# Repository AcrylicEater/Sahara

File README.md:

# Sahara - diy 3d printer filament dryer

This is the hardware and software I designed to convert a cheap food dehydrator into a more intelligent and precisely controlled device, with the aim of drying 3d printer filament.

The original product used was a Esperanza Food Dehydrator EKD003.

You set a target temperature, how long you want to dry and then it does the rest.

It is controlled by a STM32, that via relays turn on and off the fan unit and heating unit.

Be aware that this runs on **mains voltage**, so take the necessary precautions. I've implemented as much safety as I deem reasonable, but use at your own risk. I the main board with a external prefabricated 230VAC to 5VDC board and I connect an external RC snubber unit in parallel with the fan.

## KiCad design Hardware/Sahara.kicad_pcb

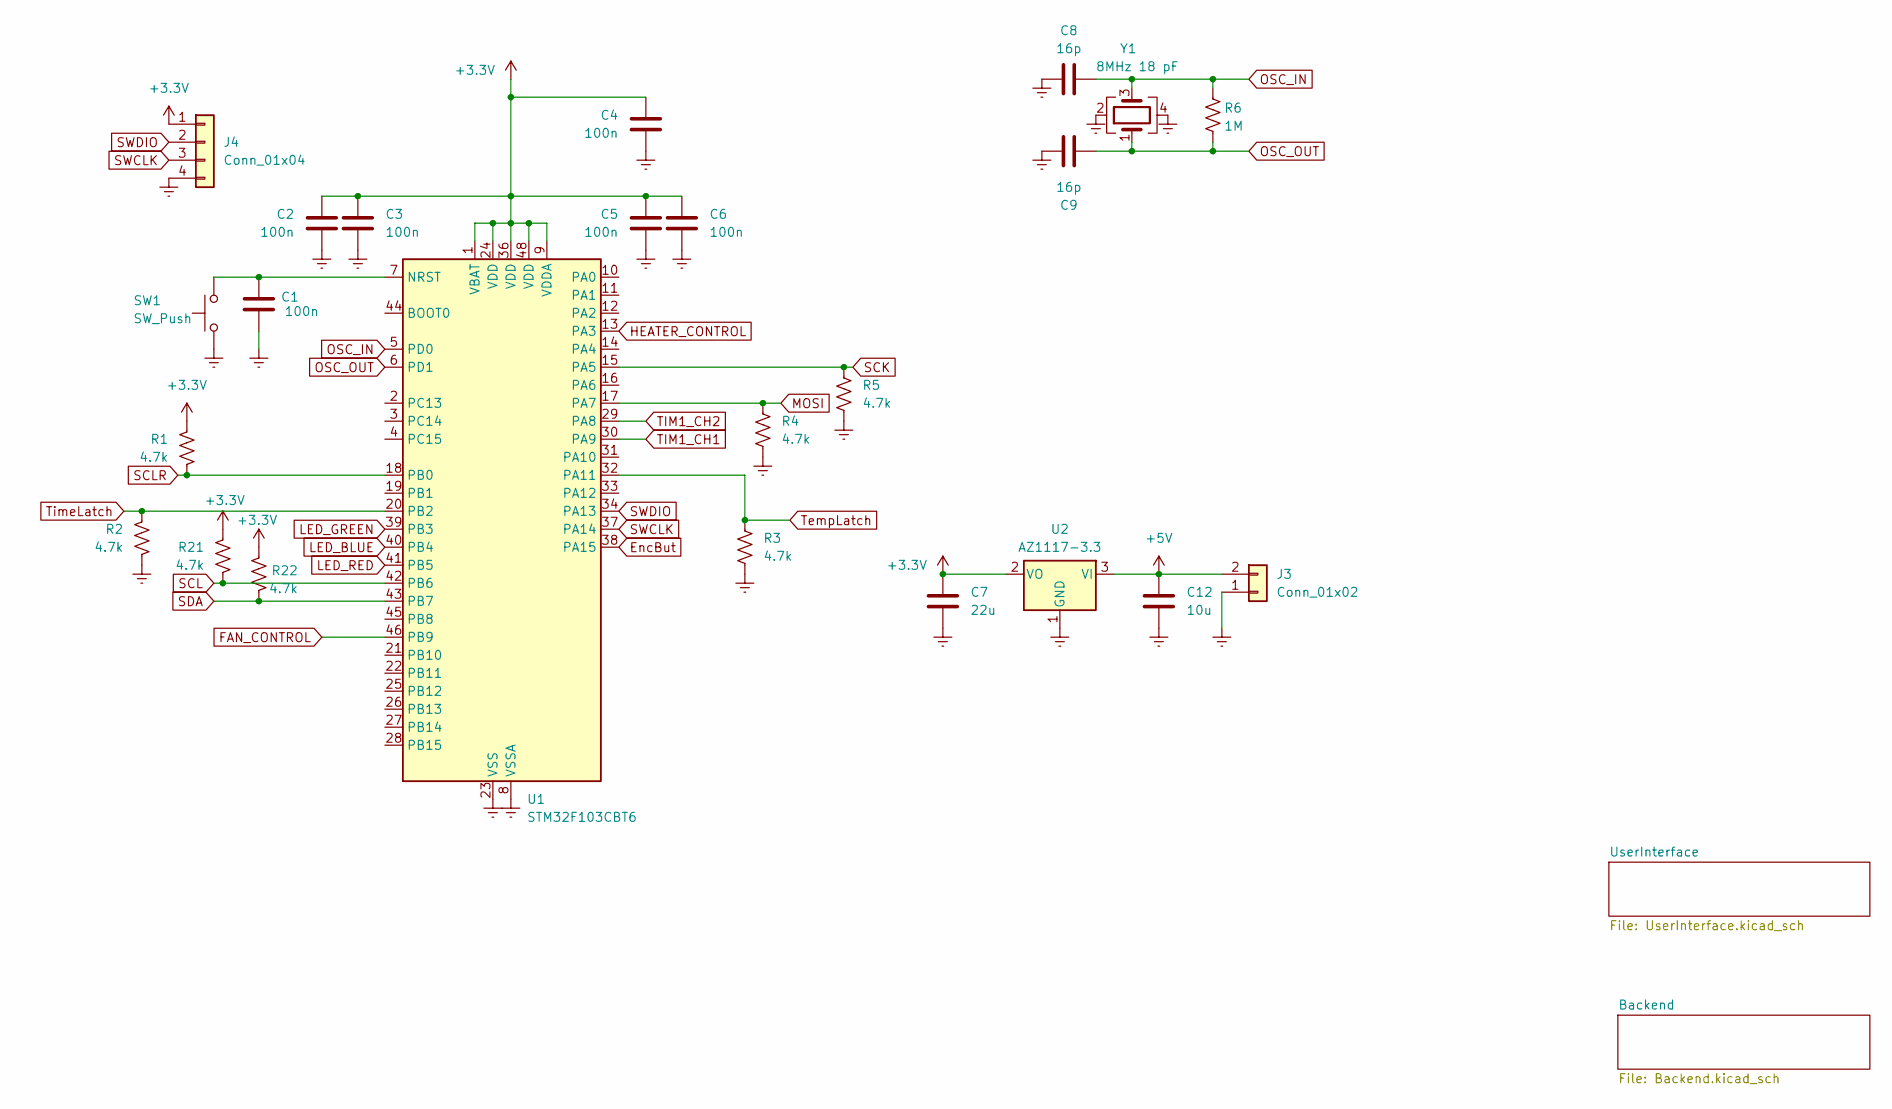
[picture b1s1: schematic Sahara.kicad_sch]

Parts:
C1, C2, C3, C4, C5, C6: 100n; C_0805_2012Metric
C7: 22u; C_0805_2012Metric
C8, C9: 16p; C_0805_2012Metric
C12: 10u; C_0805_2012Metric
J3: Conn_01x02; JST_XH_B2B-XH-AM_1x02_P2.50mm_Vertical
J4: Conn_01x04; JST_XH_B4B-XH-AM_1x04_P2.50mm_Vertical
R1, R2, R3, R4, R5, R21, R22: 4.7k; R_0805_2012Metric
R6: 1M; R_0805_2012Metric
SW1: SW_Push
U1: STM32F103CBT6; LQFP-48_7x7mm_P0.5mm
U2: AZ1117-3.3; SOT230P700X180-4N
Y1: 8MHz 18 pF; Crystal_SMD_TXC_7M-4Pin_3.2x2.5mm

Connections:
+3.3V: C2.1, C3.1, C4.1, C5.1, C6.1, C7.1, J4.1, R1.1, R21.1, R22.1, U1.1 (VBAT), U1.9 (VDDA), U1.24 (VDD), U1.36 (VDD), U1.48 (VDD), U2.2 (VO); also elsewhere on the board
+5V: C12.1, J3.2 (Pin_1), U2.3 (VI); also elsewhere on the board
Earth: C1.2, C2.2, C3.2, C4.2, C5.2, C6.2, C7.2, C8.1, C9.1, C12.2, J3.1 (Pin_2), J4.4, R2.2, R3.2, R4.2, R5.2, SW1.1, U1.8 (VSSA), U1.23 (VSS), U1.35 (VSS), U1.47 (VSS), U2.1 (GND), Y1.2, Y1.4; also elsewhere on the board
EncBut: U1.38 (PA15); also elsewhere on the board
FAN_CONTROL: U1.46 (PB9); also elsewhere on the board
HEATER_CONTROL: U1.13 (PA3); also elsewhere on the board
LED_BLUE: U1.40 (PB4); also elsewhere on the board
LED_GREEN: U1.39 (PB3); also elsewhere on the board
LED_RED: U1.41 (PB5); also elsewhere on the board
MOSI: R4.1, U1.17 (PA7); also elsewhere on the board
unnamed: C1.1, SW1.2, U1.7 (NRST)
OSC_IN: C8.2, R6.1, U1.5 (PD0), Y1.3
OSC_OUT: C9.2, R6.2, U1.6 (PD1), Y1.1
SCK: R5.1, U1.15 (PA5); also elsewhere on the board
SCL: R21.2, U1.42 (PB6); also elsewhere on the board
SCLR: R1.2, U1.18 (PB0); also elsewhere on the board
SDA: R22.2, U1.43 (PB7); also elsewhere on the board
SWCLK: J4.3, U1.37 (PA14)
SWDIO: J4.2, U1.34 (PA13)
TIM1_CH1: U1.30 (PA9); also elsewhere on the board
TIM1_CH2: U1.29 (PA8); also elsewhere on the board
TempLatch: R3.1, U1.32 (PA11); also elsewhere on the board
TimeLatch: R2.1, U1.20 (PB2); also elsewhere on the board

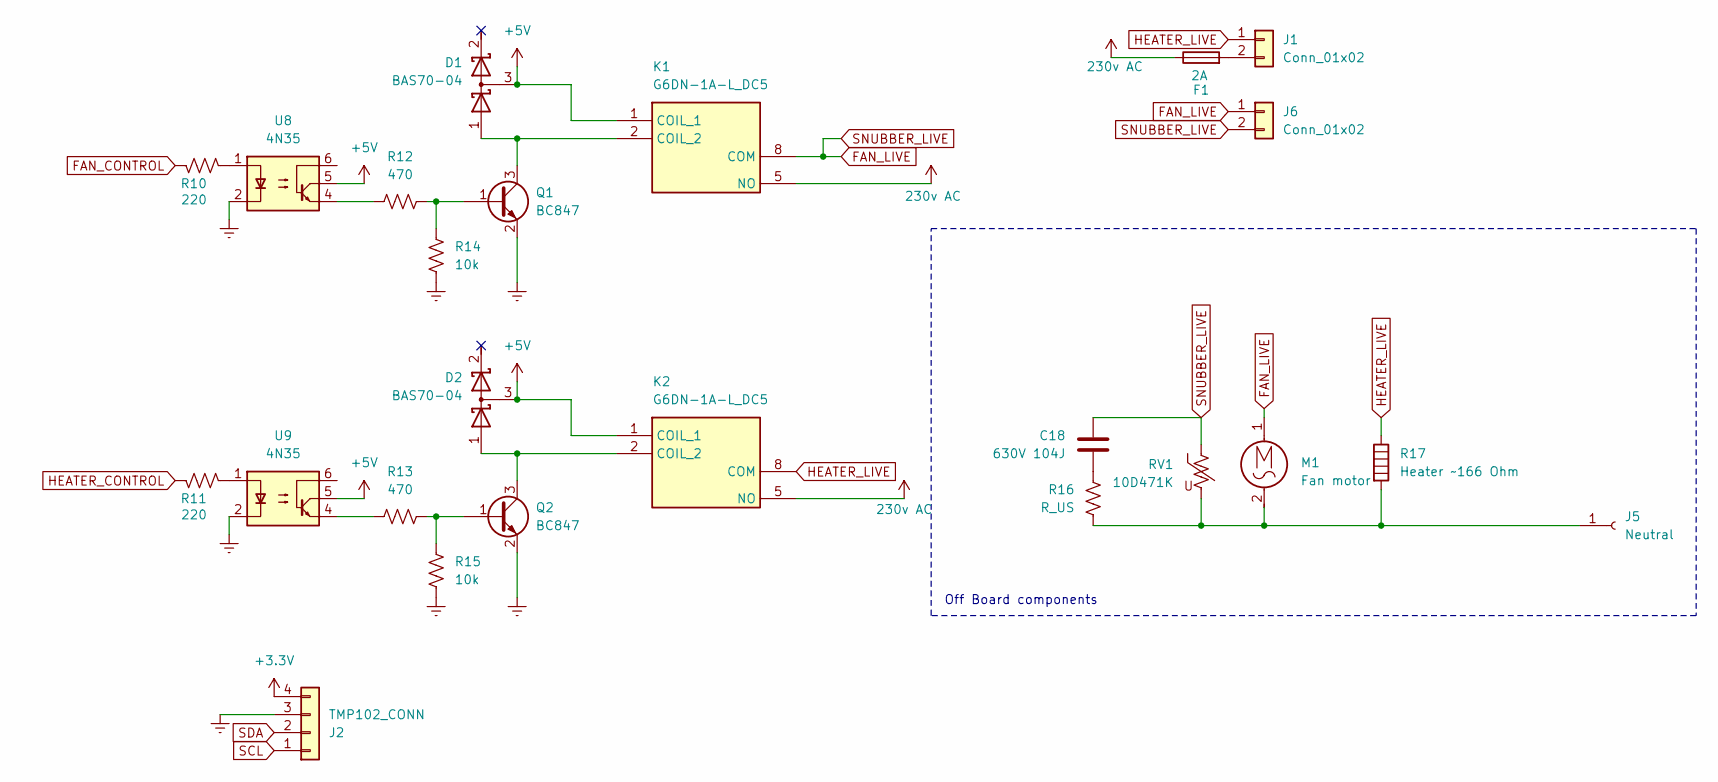
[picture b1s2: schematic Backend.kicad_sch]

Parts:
C18: 630V 104J
D1, D2: BAS70-04; SOT97P230X109-3N; Manufacturer_Part_Number BAS70-04; Mouser Part Number 821-BAS70-04
F1: 2A; WR-FSH_THT_2
J1, J6: Conn_01x02; TerminalBlock_Phoenix_PT-1,5-2-5.0-H_1x02_P5.00mm_Horizontal
J2: TMP102_CONN; JST_XH_B4B-XH-AM_1x04_P2.50mm_Vertical
J5: Neutral
K1, K2: G6DN-1A-L_DC5; G6DN-1A-L; Mouser Part Number 653-G6DN-1A-LDC5
M1: Fan motor
Q1, Q2: BC847; SOT-23
R10, R11: 220; R_0805_2012Metric
R12, R13: 470; R_0805_2012Metric
R14, R15: 10k; R_0805_2012Metric
R16: R_US
R17: Heater ~166 Ohm
RV1: 10D471K
U8, U9: 4N35; 4N35S

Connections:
230v AC: F1.1, K1.5 (NO), K2.5 (NO)
+3.3V: J2.4; also elsewhere on the board
+5V: D1.3 (common), D2.3 (common), K1.1 (COIL_1), K2.1 (COIL_1), U8.5, U9.5; also elsewhere on the board
Earth: J2.3, Q1.2 (E), Q2.2 (E), R14.1, R15.1, U8.2, U9.2; also elsewhere on the board
FAN_CONTROL: R10.2; also elsewhere on the board
FAN_LIVE: C18.1, J6.1, J6.2, K1.8 (COM), M1.1, RV1.1
HEATER_CONTROL: R11.2; also elsewhere on the board
HEATER_LIVE: J1.1, K2.8 (COM), R17.1
unnamed: C18.2, R16.1
unnamed: D1.1 (A), K1.2 (COIL_2), Q1.3 (C)
unnamed: D2.1 (A), K2.2 (COIL_2), Q2.3 (C)
unnamed: F1.2, J1.2
unnamed: J5.1, M1.2, R16.2, R17.2, RV1.2
unnamed: Q1.1 (B), R12.2, R14.2
unnamed: Q2.1 (B), R13.2, R15.2
unnamed: R10.1, U8.1
unnamed: R11.1, U9.1
unnamed: R12.1, U8.4
unnamed: R13.1, U9.4
SCL: J2.1; also elsewhere on the board
SDA: J2.2; also elsewhere on the board

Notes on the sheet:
Off Board components

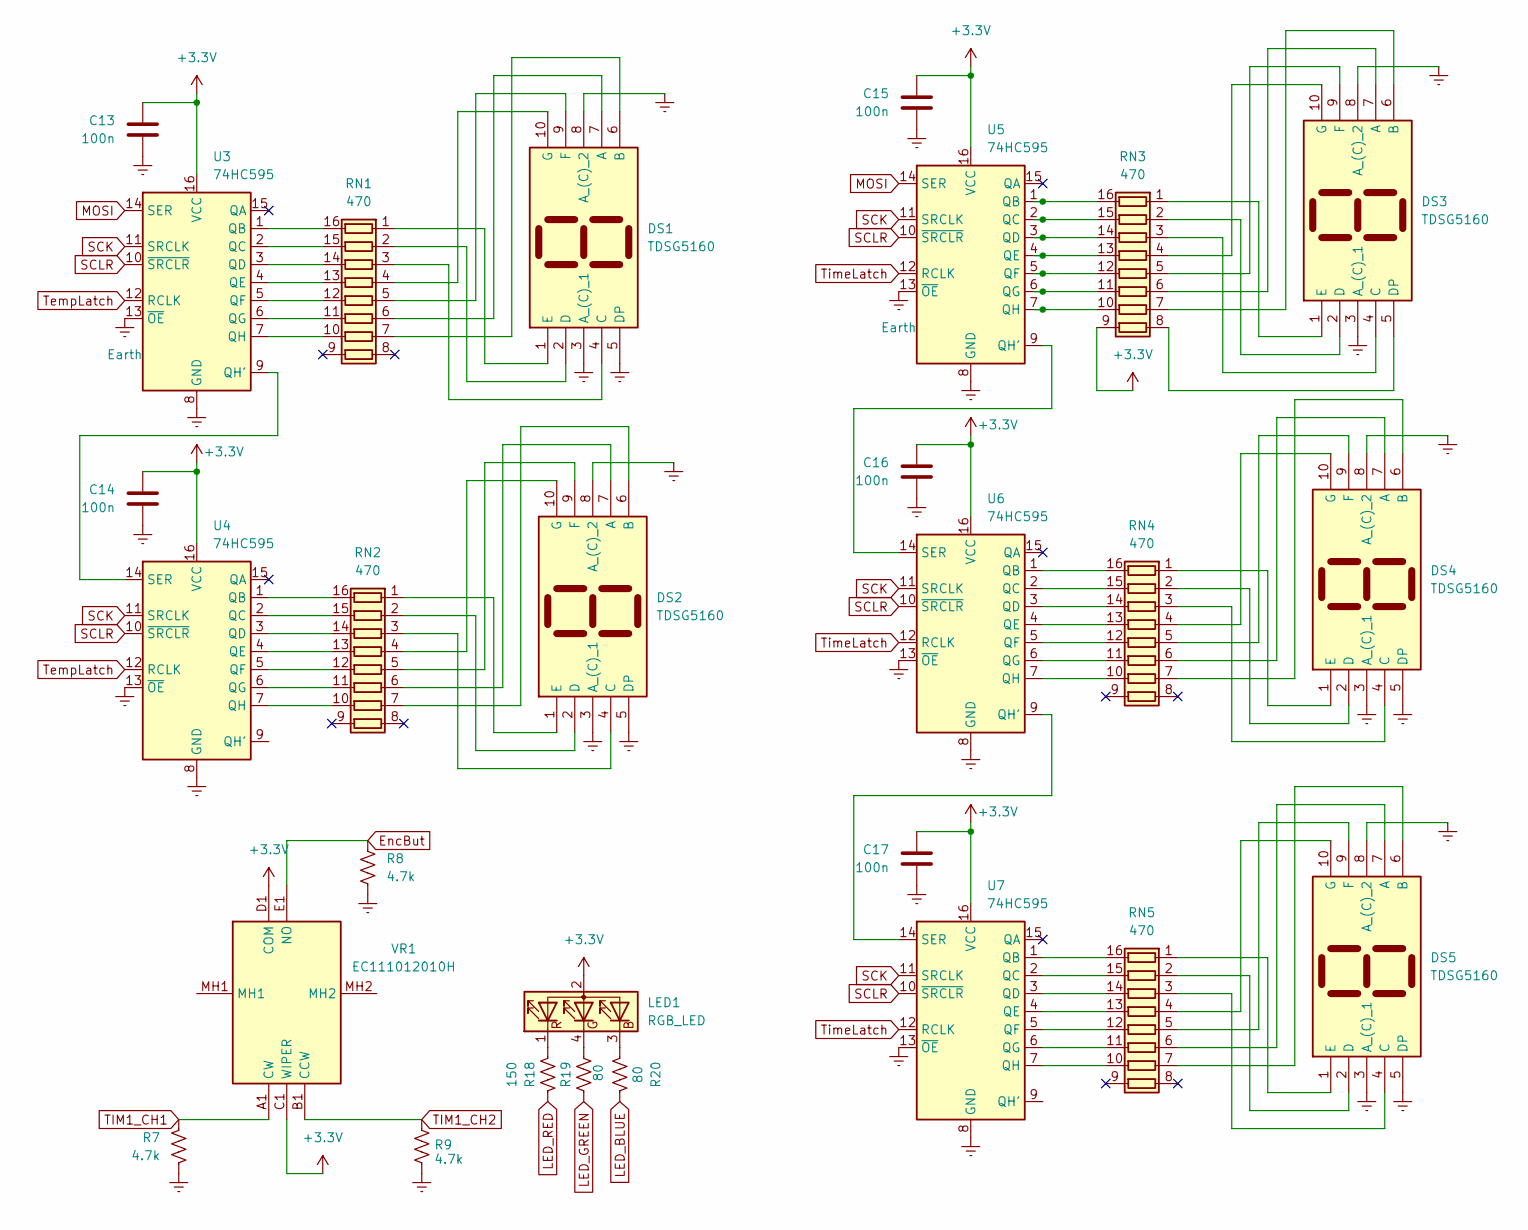
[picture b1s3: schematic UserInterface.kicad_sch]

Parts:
C13, C14, C15, C16, C17: 100n; C_0805_2012Metric
DS1, DS2, DS3, DS4, DS5: TDSG5160; Mouser Part Number 78-TDSG5160
LED1: RGB_LED; 5218559F; Manufacturer_Part_Number 521-8559F; Mouser Part Number 645-5218559F
R7, R8, R9: 4.7k; R_0805_2012Metric
R18: 150; R_0805_2012Metric
R19, R20: 80; R_0805_2012Metric
RN1, RN2, RN3, RN4, RN5: 470; EXB2HV_1
U3, U4, U5, U6, U7: 74HC595; SOIC127P600X175-16N
VR1: EC111012010H; Mouser Part Number 688-EC111012010H

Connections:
+3.3V: C13.1, C14.1, C15.1, C16.1, C17.1, LED1.2 (A), RN3.9 (R8.2), U3.16 (VCC), U4.16 (VCC), U5.16 (VCC), U6.16 (VCC), U7.16 (VCC), VR1.C1 (WIPER), VR1.D1 (COM); also elsewhere on the board
Earth: C13.2, C14.2, C15.2, C16.2, C17.2, DS1.3 (A_(C)_1), DS1.5 (DP), DS1.8 (A_(C)_2), DS2.3 (A_(C)_1), DS2.5 (DP), DS2.8 (A_(C)_2), DS3.3 (A_(C)_1), DS3.8 (A_(C)_2), DS4.3 (A_(C)_1), DS4.5 (DP), DS4.8 (A_(C)_2), DS5.3 (A_(C)_1), DS5.5 (DP), DS5.8 (A_(C)_2), R7.2, R8.2, R9.1, U3.8 (GND), U3.13 (~OE), U4.8 (GND), U4.13 (~OE), U5.8 (GND), U5.13 (~OE), U6.8 (GND), U6.13 (~OE), U7.8 (GND), U7.13 (~OE); also elsewhere on the board
EncBut: R8.1, VR1.E1 (NO); also elsewhere on the board
LED_BLUE: R20.1; also elsewhere on the board
LED_GREEN: R19.2; also elsewhere on the board
LED_RED: R18.2; also elsewhere on the board
MOSI: U3.14 (SER), U5.14 (SER); also elsewhere on the board
unnamed: DS1.7 (A), RN1.6 (R6.1)
unnamed: DS1.6 (B), RN1.7 (R7.1)
unnamed: DS1.4 (C), RN1.3 (R3.1)
unnamed: DS1.2 (D), RN1.2 (R2.1)
unnamed: DS1.1 (E), RN1.1 (R1.1)
unnamed: DS1.9 (F), RN1.5 (R5.1)
unnamed: DS1.10 (G), RN1.4 (R4.1)
unnamed: DS2.7 (A), RN2.6 (R6.1)
unnamed: DS2.6 (B), RN2.7 (R7.1)
unnamed: DS2.4 (C), RN2.3 (R3.1)
unnamed: DS2.2 (D), RN2.2 (R2.1)
unnamed: DS2.1 (E), RN2.1 (R1.1)
unnamed: DS2.9 (F), RN2.5 (R5.1)
unnamed: DS2.10 (G), RN2.4 (R4.1)
unnamed: DS3.7 (A), RN3.6 (R6.1)
unnamed: DS3.6 (B), RN3.7 (R7.1)
unnamed: DS3.4 (C), RN3.3 (R3.1)
unnamed: DS3.2 (D), RN3.2 (R2.1)
unnamed: DS3.5 (DP), RN3.8 (R8.1)
unnamed: DS3.1 (E), RN3.1 (R1.1)
unnamed: DS3.9 (F), RN3.5 (R5.1)
unnamed: DS3.10 (G), RN3.4 (R4.1)
unnamed: DS4.7 (A), RN4.6 (R6.1)
unnamed: DS4.6 (B), RN4.7 (R7.1)
unnamed: DS4.4 (C), RN4.3 (R3.1)
unnamed: DS4.2 (D), RN4.2 (R2.1)
unnamed: DS4.1 (E), RN4.1 (R1.1)
unnamed: DS4.9 (F), RN4.5 (R5.1)
unnamed: DS4.10 (G), RN4.4 (R4.1)
unnamed: DS5.7 (A), RN5.6 (R6.1)
unnamed: DS5.6 (B), RN5.7 (R7.1)
unnamed: DS5.4 (C), RN5.3 (R3.1)
unnamed: DS5.2 (D), RN5.2 (R2.1)
unnamed: DS5.1 (E), RN5.1 (R1.1)
unnamed: DS5.9 (F), RN5.5 (R5.1)
unnamed: DS5.10 (G), RN5.4 (R4.1)
unnamed: LED1.3 (BK), R20.2
unnamed: LED1.4 (GK), R19.1
unnamed: LED1.1, R18.1
unnamed: RN1.16 (R1.2), U3.1 (QB)
unnamed: RN1.15 (R2.2), U3.2 (QC)
unnamed: RN1.14 (R3.2), U3.3 (QD)
unnamed: RN1.13 (R4.2), U3.4 (QE)
unnamed: RN1.12 (R5.2), U3.5 (QF)
unnamed: RN1.11 (R6.2), U3.6 (QG)
unnamed: RN1.10 (R7.2), U3.7 (QH)
unnamed: RN2.16 (R1.2), U4.1 (QB)
unnamed: RN2.15 (R2.2), U4.2 (QC)
unnamed: RN2.14 (R3.2), U4.3 (QD)
unnamed: RN2.13 (R4.2), U4.4 (QE)
unnamed: RN2.12 (R5.2), U4.5 (QF)
unnamed: RN2.11 (R6.2), U4.6 (QG)
unnamed: RN2.10 (R7.2), U4.7 (QH)
unnamed: RN3.16 (R1.2), U5.1 (QB)
unnamed: RN3.15 (R2.2), U5.2 (QC)
unnamed: RN3.14 (R3.2), U5.3 (QD)
unnamed: RN3.13 (R4.2), U5.4 (QE)
unnamed: RN3.12 (R5.2), U5.5 (QF)
unnamed: RN3.11 (R6.2), U5.6 (QG)
unnamed: RN3.10 (R7.2), U5.7 (QH)
unnamed: RN4.16 (R1.2), U6.1 (QB)
unnamed: RN4.15 (R2.2), U6.2 (QC)
unnamed: RN4.14 (R3.2), U6.3 (QD)
unnamed: RN4.13 (R4.2), U6.4 (QE)
unnamed: RN4.12 (R5.2), U6.5 (QF)
unnamed: RN4.11 (R6.2), U6.6 (QG)
unnamed: RN4.10 (R7.2), U6.7 (QH)
unnamed: RN5.16 (R1.2), U7.1 (QB)
unnamed: RN5.15 (R2.2), U7.2 (QC)
unnamed: RN5.14 (R3.2), U7.3 (QD)
unnamed: RN5.13 (R4.2), U7.4 (QE)
unnamed: RN5.12 (R5.2), U7.5 (QF)
unnamed: RN5.11 (R6.2), U7.6 (QG)
unnamed: RN5.10 (R7.2), U7.7 (QH)
unnamed: U3.9 (QH'), U4.14 (SER)
unnamed: U5.9 (QH'), U6.14 (SER)
unnamed: U6.9 (QH'), U7.14 (SER)
SCK: U3.11 (SRCLK), U4.11 (SRCLK), U5.11 (SRCLK), U6.11 (SRCLK), U7.11 (SRCLK); also elsewhere on the board
SCLR: U3.10 (~SRCLR), U4.10 (~SRCLR), U5.10 (~SRCLR), U6.10 (~SRCLR), U7.10 (~SRCLR); also elsewhere on the board
TIM1_CH1: R7.1, VR1.A1 (CW); also elsewhere on the board
TIM1_CH2: R9.2, VR1.B1 (CCW); also elsewhere on the board
TempLatch: U3.12 (RCLK), U4.12 (RCLK); also elsewhere on the board
TimeLatch: U5.12 (RCLK), U6.12 (RCLK), U7.12 (RCLK); also elsewhere on the board

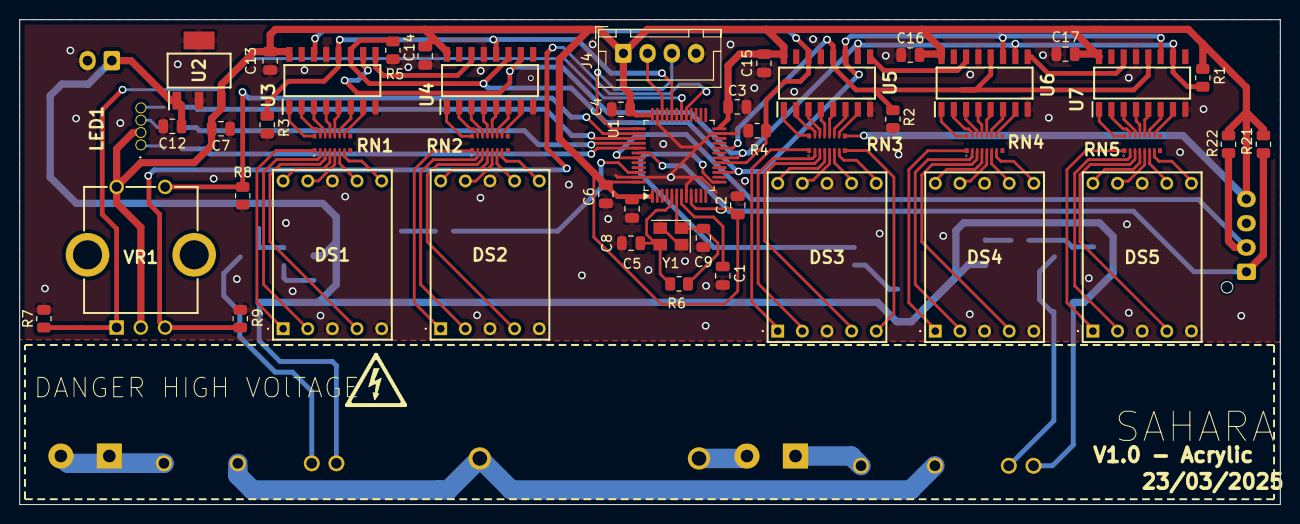
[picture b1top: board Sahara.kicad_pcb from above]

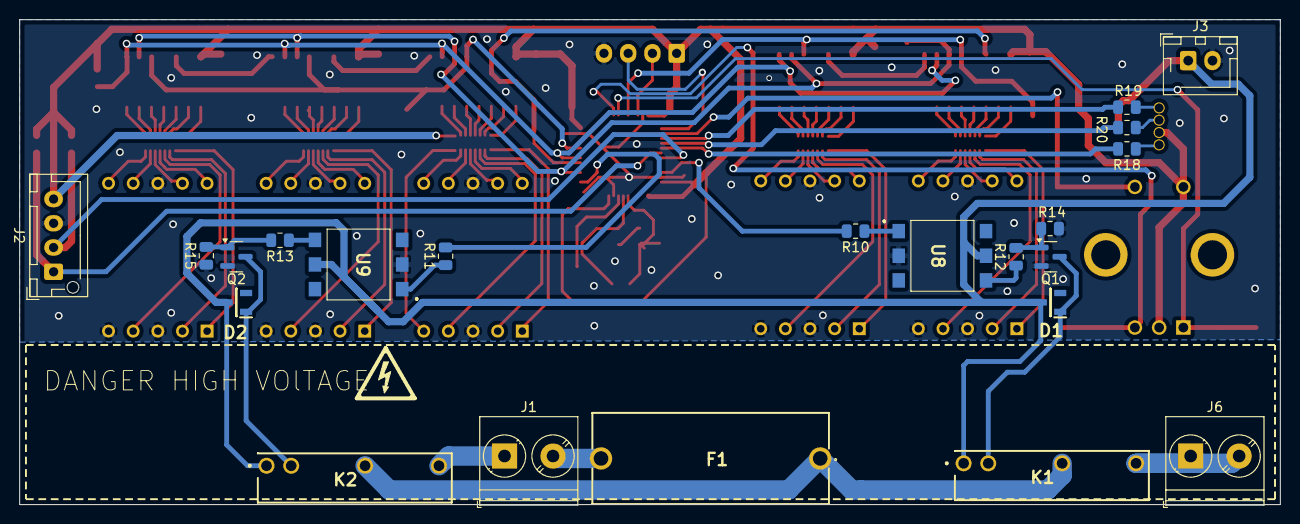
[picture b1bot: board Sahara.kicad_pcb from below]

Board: 2 copper layers, 130.0 x 50.0 mm, 69 parts (22 on the bottom side), 112 nets.

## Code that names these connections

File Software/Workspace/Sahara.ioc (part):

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Mcu.Name=STM32F103C(8-B)Tx
Mcu.Package=LQFP48
Mcu.UserName=STM32F103CBTx
PA13.Mode=Serial_Wire
PA13.Signal=SYS_JTMS-SWDIO
PA14.Mode=Serial_Wire
PA14.Signal=SYS_JTCK-SWCLK
PA15.GPIOParameters=GPIO_Label
PA15.GPIO_Label=EncBut
PA15.Signal=GPIO_Input
PA3.GPIOParameters=GPIO_Label
PA3.GPIO_Label=HEATER_RELAY
PA3.Signal=GPIO_Output
PA5.Mode=TX_Only_Simplex_Unidirect_Master
PA5.Signal=SPI1_SCK
PA7.Mode=TX_Only_Simplex_Unidirect_Master
PA7.Signal=SPI1_MOSI
PA8.Signal=S_TIM1_CH1
PA9.Signal=S_TIM1_CH2
PB0.GPIOParameters=PinState,GPIO_Label
PB0.GPIO_Label=SRCLR
PB0.PinState=GPIO_PIN_SET
PB0.Signal=GPIO_Output
PB10.GPIOParameters=PinState,GPIO_Label
PB10.GPIO_Label=TEMP_LATCH
PB10.PinState=GPIO_PIN_RESET
PB10.Signal=GPIO_Output
PB2.GPIOParameters=GPIO_Label
PB2.GPIO_Label=TIME_LATCH
PB2.Signal=GPIO_Output
PB3.GPIOParameters=PinState,GPIO_Label
PB3.GPIO_Label=GREEN_LED
PB3.PinState=GPIO_PIN_SET
PB3.Signal=GPIO_Output
PB4.GPIOParameters=PinState,GPIO_Label
PB4.GPIO_Label=BLUE_LED
PB4.PinState=GPIO_PIN_SET
PB4.Signal=GPIO_Output
PB5.GPIOParameters=PinState,GPIO_Label
PB5.GPIO_Label=RED_LED
PB5.PinState=GPIO_PIN_SET
PB5.Signal=GPIO_Output
PB6.GPIOParameters=GPIO_Mode
PB6.GPIO_Mode=GPIO_MODE_AF_OD
PB6.Mode=I2C
PB6.Signal=I2C1_SCL
PB7.GPIOParameters=GPIO_Speed,GPIO_Mode
PB7.GPIO_Mode=GPIO_MODE_AF_OD
PB7.GPIO_Speed=GPIO_SPEED_FREQ_HIGH
PB7.Mode=I2C
PB7.Signal=I2C1_SDA
PB9.GPIOParameters=GPIO_Label
PB9.GPIO_Label=FAN_RELAY
PB9.Signal=GPIO_Output
PD0-OSC_IN.Mode=HSE-External-Oscillator
PD0-OSC_IN.Signal=RCC_OSC_IN
PD1-OSC_OUT.Mode=HSE-External-Oscillator
PD1-OSC_OUT.Signal=RCC_OSC_OUT
RCC.SYSCLKFreq_VALUE=72000000
RCC.SYSCLKSource=RCC_SYSCLKSOURCE_PLLCLK
board=custom

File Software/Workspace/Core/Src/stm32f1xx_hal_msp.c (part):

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
    __HAL_RCC_GPIOB_CLK_ENABLE();
    /**I2C1 GPIO Configuration
    PB6     ------> I2C1_SCL
    PB7     ------> I2C1_SDA
    */
    GPIO_InitStruct.Pin = GPIO_PIN_6|GPIO_PIN_7;
    GPIO_InitStruct.Mode = GPIO_MODE_AF_OD;
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    __HAL_RCC_I2C1_CLK_DISABLE();

    /**I2C1 GPIO Configuration
    PB6     ------> I2C1_SCL
    PB7     ------> I2C1_SDA
    */
    HAL_GPIO_DeInit(GPIOB, GPIO_PIN_6);

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
    __HAL_RCC_GPIOA_CLK_ENABLE();
    /**SPI1 GPIO Configuration
    PA5     ------> SPI1_SCK
    PA7     ------> SPI1_MOSI
    */
    GPIO_InitStruct.Pin = GPIO_PIN_5|GPIO_PIN_7;
    GPIO_InitStruct.Mode = GPIO_MODE_AF_PP;
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    __HAL_RCC_SPI1_CLK_DISABLE();

    /**SPI1 GPIO Configuration
    PA5     ------> SPI1_SCK
    PA7     ------> SPI1_MOSI
    */
    HAL_GPIO_DeInit(GPIOA, GPIO_PIN_5|GPIO_PIN_7);

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
    __HAL_RCC_GPIOA_CLK_ENABLE();
    /**TIM1 GPIO Configuration
    PA8     ------> TIM1_CH1
    PA9     ------> TIM1_CH2
    */
    GPIO_InitStruct.Pin = GPIO_PIN_8|GPIO_PIN_9;
    GPIO_InitStruct.Mode = GPIO_MODE_INPUT;
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    __HAL_RCC_TIM1_CLK_DISABLE();

    /**TIM1 GPIO Configuration
    PA8     ------> TIM1_CH1
    PA9     ------> TIM1_CH2
    */
    HAL_GPIO_DeInit(GPIOA, GPIO_PIN_8|GPIO_PIN_9);

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
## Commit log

2025-03-11 initial commit of project files
2025-03-11 schematic update
2025-03-12 Safety features on mains voltage
2025-03-12 ignore backups
2025-03-19 added footprints
2025-03-23 Added temperature sensor and I2C setup, started PCB layout
2025-03-25 Software stuff
2025-03-25 update gitignore
2025-03-26 Almost finished PCB
2025-03-28 slight schematic update, finished pcb(for now)

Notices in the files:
Software/Workspace/Core/Src/stm32f1xx_hal_msp.c:
Copyright (c) 2024 STMicroelectronics.
All rights reserved.
This software is licensed under terms that can be found in the LICENSE file
